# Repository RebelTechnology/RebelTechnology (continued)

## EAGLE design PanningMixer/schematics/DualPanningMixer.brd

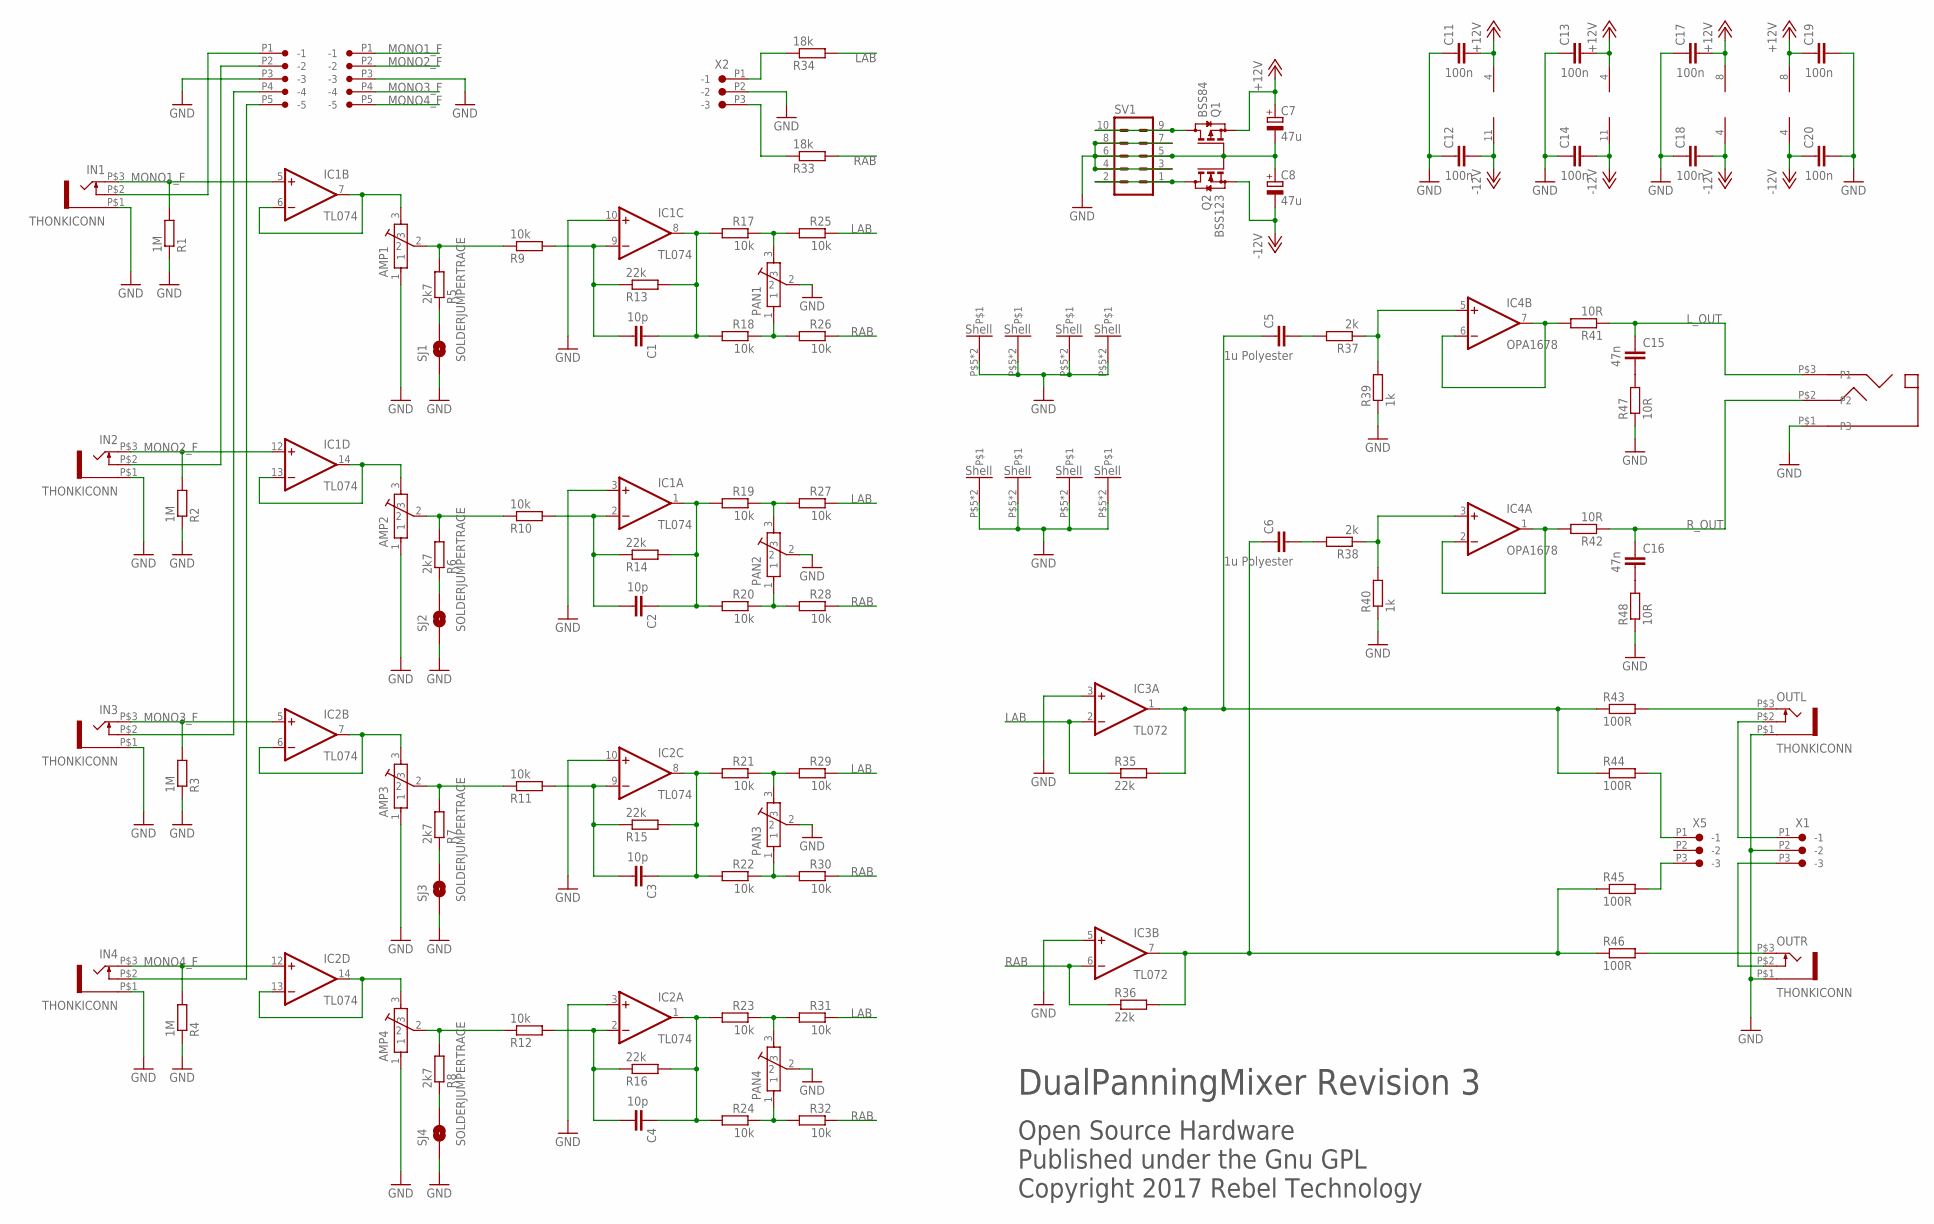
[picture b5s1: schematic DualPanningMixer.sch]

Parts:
AMP1, AMP2, AMP3, AMP4: POT-ALPS-RK09L1140
C1, C2, C3, C4: 10p; C0603
C5, C6: 1u Polyester; C1210
C7, C8: 47u; UD-5X5,8_NICHICON
C11, C12, C13, C14, C17, C18, C19, C20: 100n; C0603
C15, C16: 47n; C0603
IC1, IC2: TL074; SO14
IC3: TL072; SO08
IC4: OPA1678; SO08
IN1, IN2, IN3, IN4: THONKICONN
OUTHP: THONKICONN_STEREO
OUTL: THONKICONN
OUTR: THONKICONN
PAN1, PAN2, PAN3, PAN4: POT-ALPS-RK09L1140
Q1: BSS84; SOT23
Q2: BSS123; SOT23
R1, R2, R3, R4: 1M; 0603
R5, R6, R7, R8: 2k7; 0603
R9, R10, R11, R12, R17, R18, R19, R20, R21, R22, R23, R24, R25, R26, R27, R28, R29, R30, R31, R32: 10k; 0603
R13, R14, R15, R16, R35, R36: 22k; 0603
R33, R34: 18k; 0603
R37, R38: 2k; 0603
R39, R40: 1k; 0603
R41, R42, R47, R48: 10R; 0603
R43, R44, R45, R46: 100R; 0603
SJ1, SJ2, SJ3, SJ4: SOLDERJUMPERTRACE; SJ_2S-TRACE
SV1: MA05-2
X1, X2, X5: CON-JST_PH_3W
X3, X4: CON-JST_PH_5W

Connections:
+12V: C7.+, C11.2, C13.2, C17.2, C19.1, IC1.4 (V+), IC2.4 (V+), IC3.8 (V+), IC4.8 (V+), Q1.2 (S)
-12V: C8.-, C12.2, C14.2, C18.2, C20.1, IC1.11 (V-), IC2.11 (V-), IC3.4 (V-), IC4.4 (V-), Q2.2 (S)
GND: AMP1.1, AMP1.P$5, AMP1.P$6, AMP2.1, AMP2.P$5, AMP2.P$6, AMP3.1, AMP3.P$5, AMP3.P$6, AMP4.1, AMP4.P$5, AMP4.P$6, C7.-, C8.+, C11.1, C12.1, C13.1, C14.1, C17.1, C18.1, C19.2, C20.2, IC1.3 (+IN), IC1.10 (+IN), IC2.3 (+IN), IC2.10 (+IN), IC3.3 (+IN), IC3.5 (+IN), IN1.P$1 (5), IN2.P$1 (5), IN3.P$1 (5), IN4.P$1 (5), OUTHP.P$1 (P3), OUTL.P$1 (5), OUTR.P$1 (5), PAN1.2, PAN1.P$5, PAN1.P$6, PAN2.2, PAN2.P$5, PAN2.P$6, PAN3.2, PAN3.P$5, PAN3.P$6, PAN4.2, PAN4.P$5, PAN4.P$6, Q1.1 (G), Q2.1 (G), R1.1, R2.1, R3.1, R4.1, R39.1, R40.1, R47.1, R48.1, SJ1.1, SJ2.1, SJ3.1, SJ4.1, SV1.3, SV1.4, SV1.5, SV1.6, SV1.7, SV1.8, X1.P2 (-2), X2.P2 (-2), X3.P3 (-3), X4.P3 (-3)
LAB: IC3.2 (-IN), R25.1, R27.1, R29.1, R31.1, R34.2, R35.1
L_OUT: C15.1, OUTHP.P$3 (P1), R41.1
MONO1: AMP1.3, IC1.6 (-IN), IC1.7 (OUT)
MONO1_F: IC1.5 (+IN), IN1.P$3 (3), R1.2, X3.P1 (-1)
MONO2: AMP2.3, IC1.13 (-IN), IC1.14 (OUT)
MONO2_F: IC1.12 (+IN), IN2.P$3 (3), R2.2, X3.P2 (-2)
MONO3: AMP3.3, IC2.6 (-IN), IC2.7 (OUT)
MONO3_F: IC2.5 (+IN), IN3.P$3 (3), R3.2, X3.P4 (-4)
MONO4: AMP4.3, IC2.13 (-IN), IC2.14 (OUT)
MONO4_F: IC2.12 (+IN), IN4.P$3 (3), R4.2, X3.P5 (-5)
unnamed: AMP4.2, R8.2, R12.1
unnamed: IN2.P$2 (4), X4.P2 (-2)
unnamed: C5.1, IC3.1 (OUT), R35.2, R43.1, R44.1
unnamed: IN1.P$2 (4), X4.P1 (-1)
unnamed: C6.1, IC3.7 (OUT), R36.2, R45.1, R46.1
unnamed: IN3.P$2 (4), X4.P4 (-4)
unnamed: IC4.3 (+IN), R38.1, R40.2
unnamed: AMP1.2, R5.2, R9.1
unnamed: C1.2, IC1.9 (-IN), R9.2, R13.1
unnamed: AMP3.2, R7.2, R11.1
unnamed: AMP2.2, R6.2, R10.1
unnamed: R5.1, SJ1.2
unnamed: IC4.5 (+IN), R37.1, R39.2
unnamed: R33.1, X2.P3 (-3)
unnamed: IN4.P$2 (4), X4.P5 (-5)
unnamed: R6.1, SJ2.2
unnamed: PAN1.1, R18.1, R26.2
unnamed: PAN1.3, R17.1, R25.2
unnamed: R7.1, SJ3.2
unnamed: R8.1, SJ4.2
unnamed: C1.1, IC1.8 (OUT), R13.2, R17.2, R18.2
unnamed: R34.1, X2.P1 (-1)
unnamed: C4.1, IC2.1 (OUT), R16.2, R23.2, R24.2
unnamed: C2.1, IC1.1 (OUT), R14.2, R19.2, R20.2
unnamed: PAN2.3, R19.1, R27.2
unnamed: OUTL.P$3 (3), R43.2
unnamed: PAN2.1, R20.1, R28.2
unnamed: PAN3.3, R21.1, R29.2
unnamed: C3.1, IC2.8 (OUT), R15.2, R21.2, R22.2
unnamed: PAN3.1, R22.1, R30.2
unnamed: PAN4.3, R23.1, R31.2
unnamed: OUTR.P$3 (3), R46.2
unnamed: PAN4.1, R24.1, R32.2
unnamed: C16.2, R48.2
unnamed: C2.2, IC1.2 (-IN), R10.2, R14.1
unnamed: Q2.3 (D), SV1.1, SV1.2
unnamed: C3.2, IC2.9 (-IN), R11.2, R15.1
unnamed: Q1.3 (D), SV1.9, SV1.10
unnamed: C4.2, IC2.2 (-IN), R12.2, R16.1
unnamed: C15.2, R47.2
unnamed: C5.2, R37.2
unnamed: IC4.6 (-IN), IC4.7 (OUT), R41.2
unnamed: IC4.1 (OUT), IC4.2 (-IN), R42.2
unnamed: C6.2, R38.2
OUT_NS_L: R44.2, X5.P1 (-1)
OUT_NS_R: R45.2, X5.P3 (-3)
OUT_SW_L: OUTL.P$2 (4), X1.P1 (-1)
OUT_SW_R: OUTR.P$2 (4), X1.P3 (-3)
RAB: IC3.6 (-IN), R26.1, R28.1, R30.1, R32.1, R33.2, R36.1
R_OUT: C16.1, OUTHP.P$2 (P2), R42.1

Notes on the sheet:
Open Source Hardware Published under the Gnu GPL Copyright 2017 Rebel Technology
DualPanningMixer Revision 3

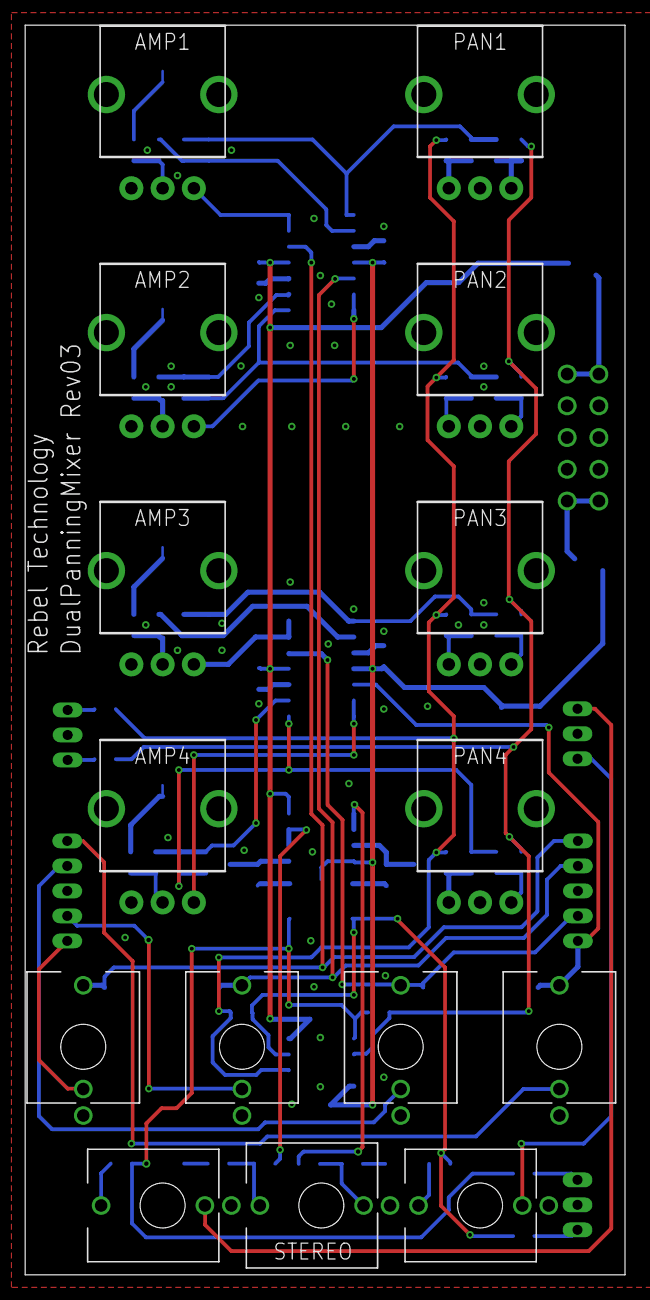
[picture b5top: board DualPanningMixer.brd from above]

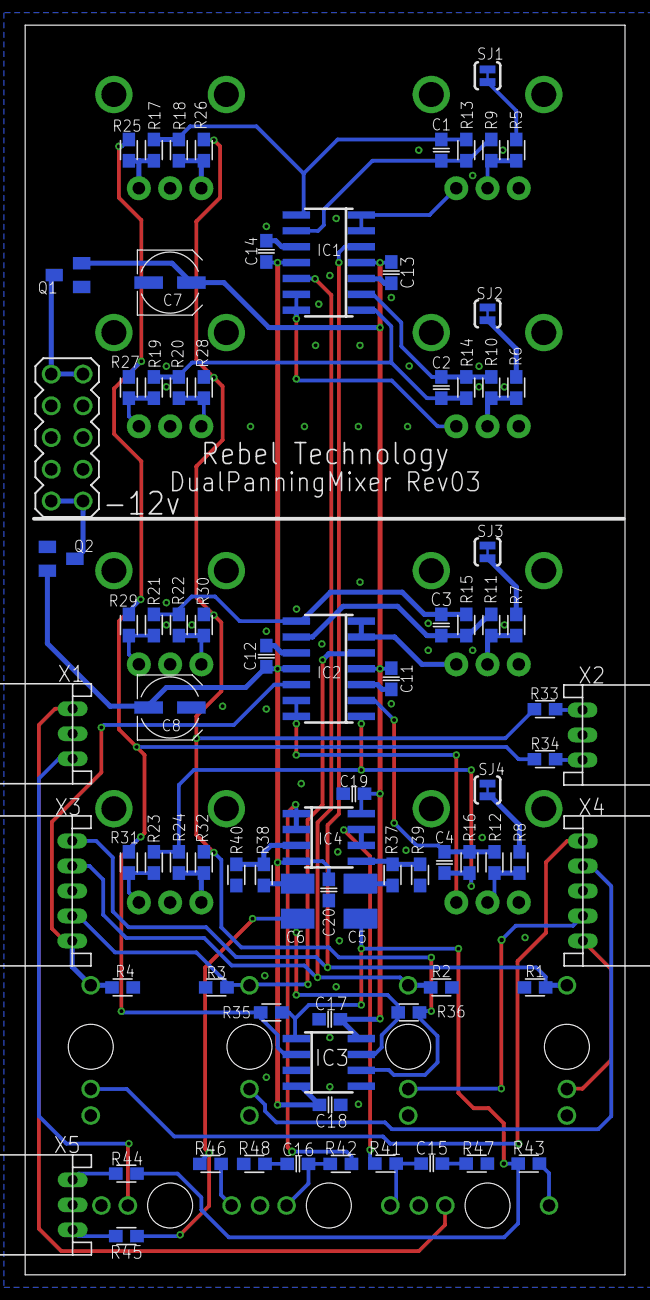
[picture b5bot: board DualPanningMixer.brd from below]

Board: 2 copper layers, 48.0 x 100.0 mm, 97 parts (82 on the bottom side), 63 nets.

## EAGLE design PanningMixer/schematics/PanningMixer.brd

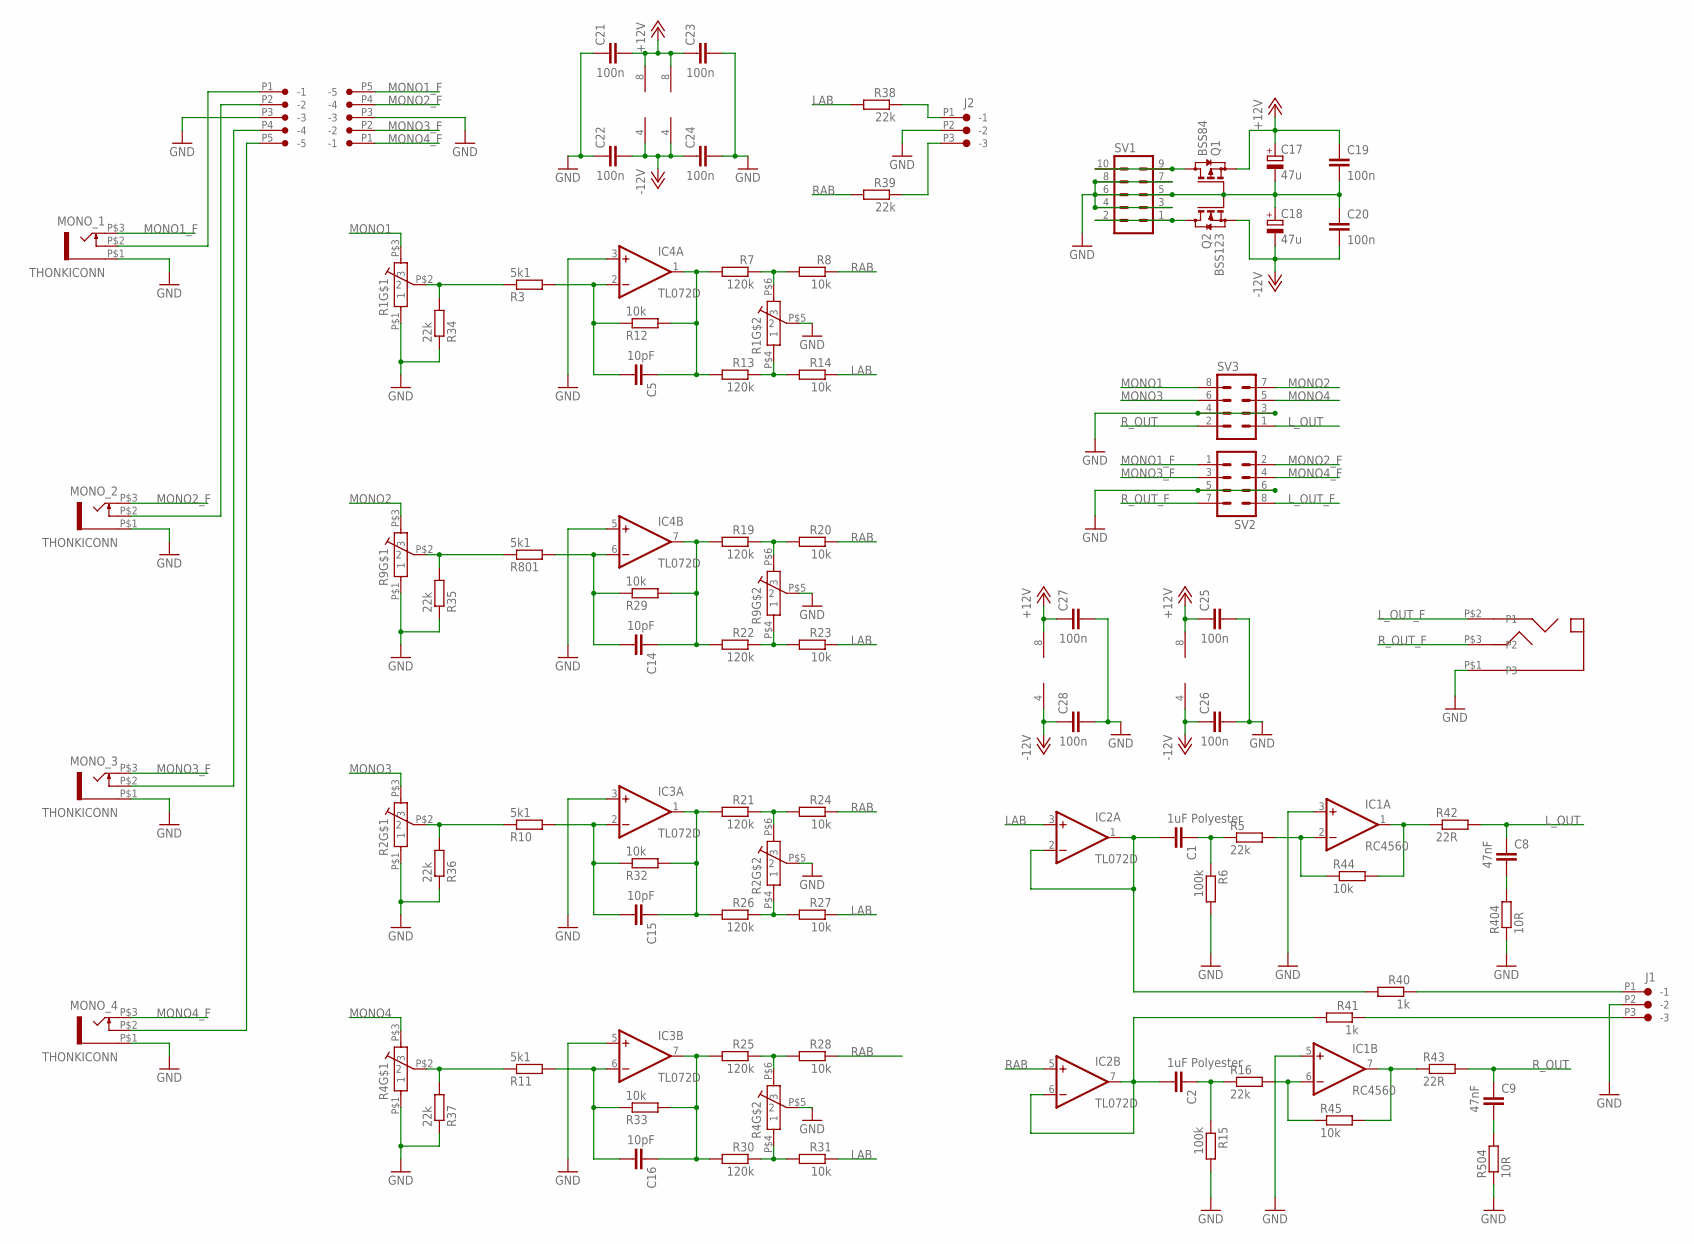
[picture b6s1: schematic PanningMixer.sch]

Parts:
C1, C2: 1uF Polyester; C1210
C5, C14, C15, C16: 10pF; C0603
C8, C9: 47nF; C0603
C17, C18: 47u; PANASONIC_B
C19, C20, C21, C22, C23, C24, C25, C26, C27, C28: 100n; C0603
IC1: RC4560; SO08
IC2, IC3, IC4: TL072D; SO08
J1, J2: CON-JST_PH_3W
MONO_1, MONO_2, MONO_3, MONO_4: THONKICONN
Q1: BSS84; SOT23
Q2: BSS123; SOT23
R1, R2, R4, R9: POT-ALPHA_DUAL_9MM; POT-ALPA_DUAL_9MM
R3, R10, R11, R801: 5k1; 0603
R5, R16, R34, R35, R36, R37, R38, R39: 22k; 0603
R6, R15: 100k; 0603
R7, R13, R19, R21, R22, R25, R26, R30: 120k; 0603
R8, R12, R14, R20, R23, R24, R27, R28, R29, R31, R32, R33, R44, R45: 10k; 0603
R40, R41: 1k; 0603
R42, R43: 22R; 0603
R404, R504: 10R; 0603
SV1: MA05-2
SV2, SV3: MA04-2
U1: CON-PROSIGNAL_MJ-355W
U2, U4: CON-JST_PH_5W

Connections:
+12V: C17.+, C19.1, C21.2, C23.1, C25.1, C27.1, IC1.8 (V+), IC2.8 (V+), IC3.8 (V+), IC4.8 (V+), Q1.2 (S)
-12V: C18.-, C20.2, C22.2, C24.1, C26.1, C28.1, IC1.4 (V-), IC2.4 (V-), IC3.4 (V-), IC4.4 (V-), Q2.2 (S)
GND: C17.-, C18.+, C19.2, C20.1, C21.1, C22.1, C23.2, C24.2, C25.2, C26.2, C27.2, C28.2, IC1.3 (+IN), IC1.5 (+IN), IC3.3 (+IN), IC3.5 (+IN), IC4.3 (+IN), IC4.5 (+IN), J1.P2 (-2), J2.P2 (-2), Q1.1 (G), Q2.1 (G), R1.P$1 (1), R1.P$5 (2), R2.P$1 (1), R2.P$5 (2), R4.P$1 (1), R4.P$5 (2), R6.2, R9.P$1 (1), R9.P$5 (2), R15.2, R34.1, R35.1, R36.1, R37.1, R404.1, R504.1, SV1.3, SV1.4, SV1.5, SV1.6, SV1.7, SV1.8, SV3.3, SV3.4
GND_A: MONO_1.P$1 (5), MONO_2.P$1 (5), MONO_3.P$1 (5), MONO_4.P$1 (5), SV2.5, SV2.6, U1.P$1 (P3), U2.P3 (-3), U4.P3 (-3)
LAB: IC2.3 (+IN), R14.1, R23.1, R27.1, R31.1, R38.2
L_OUT: C8.1, R42.2, SV3.1
L_OUT_F: SV2.8, U1.P$2 (P1)
MONO1: R1.P$3 (3), SV3.8
MONO1_F: MONO_1.P$3 (3), SV2.1, U4.P5 (-5)
MONO2: R9.P$3 (3), SV3.7
MONO2_F: MONO_2.P$3 (3), SV2.2, U4.P4 (-4)
MONO3: R2.P$3 (3), SV3.6
MONO3_F: MONO_3.P$3 (3), SV2.3, U4.P2 (-2)
MONO4: R4.P$3 (3), SV3.5
MONO4_F: MONO_4.P$3 (3), SV2.4, U4.P1 (-1)
unnamed: R4.P$2 (2), R11.1, R37.2
unnamed: MONO_2.P$2 (4), U2.P2 (-2)
unnamed: MONO_1.P$2 (4), U2.P1 (-1)
unnamed: C1.1, R5.1, R6.1
unnamed: MONO_3.P$2 (4), U2.P4 (-4)
unnamed: IC1.2 (-IN), R5.2, R44.1
unnamed: R1.P$2 (2), R3.1, R34.2
unnamed: C5.2, IC4.2 (-IN), R3.2, R12.1
unnamed: R2.P$2 (2), R10.1, R36.2
unnamed: R9.P$2 (2), R35.2, R801.1
unnamed: C9.2, R504.2
unnamed: J2.P1 (-1), R38.1
unnamed: MONO_4.P$2 (4), U2.P5 (-5)
unnamed: J1.P1 (-1), R40.1
unnamed: R1.P$4 (1), R13.1, R14.2
unnamed: R1.P$6 (3), R7.1, R8.2
unnamed: J1.P3 (-3), R41.1
unnamed: C8.2, R404.2
unnamed: C2.1, R15.1, R16.1
unnamed: C5.1, IC4.1 (OUT), R7.2, R12.2, R13.2
unnamed: J2.P3 (-3), R39.1
unnamed: C16.1, IC3.7 (OUT), R25.2, R30.2, R33.2
unnamed: C14.1, IC4.7 (OUT), R19.2, R22.2, R29.2
unnamed: IC1.1 (OUT), R42.1, R44.2
unnamed: IC1.6 (-IN), R16.2, R45.1
unnamed: C1.2, IC2.1 (OUT), IC2.2 (-IN), R40.2
unnamed: IC1.7 (OUT), R43.1, R45.2
unnamed: C2.2, IC2.6 (-IN), IC2.7 (OUT), R41.2
unnamed: R9.P$6 (3), R19.1, R20.2
unnamed: R9.P$4 (1), R22.1, R23.2
unnamed: R2.P$6 (3), R21.1, R24.2
unnamed: C15.1, IC3.1 (OUT), R21.2, R26.2, R32.2
unnamed: R2.P$4 (1), R26.1, R27.2
unnamed: R4.P$6 (3), R25.1, R28.2
unnamed: R4.P$4 (1), R30.1, R31.2
unnamed: C14.2, IC4.6 (-IN), R29.1, R801.2
unnamed: Q2.3 (D), SV1.1, SV1.2
unnamed: C15.2, IC3.2 (-IN), R10.2, R32.1
unnamed: Q1.3 (D), SV1.9, SV1.10
unnamed: C16.2, IC3.6 (-IN), R11.2, R33.1
RAB: IC2.5 (+IN), R8.1, R20.1, R24.1, R28.1, R39.2
R_OUT: C9.1, R43.2, SV3.2
R_OUT_F: SV2.7, U1.P$3 (P2)

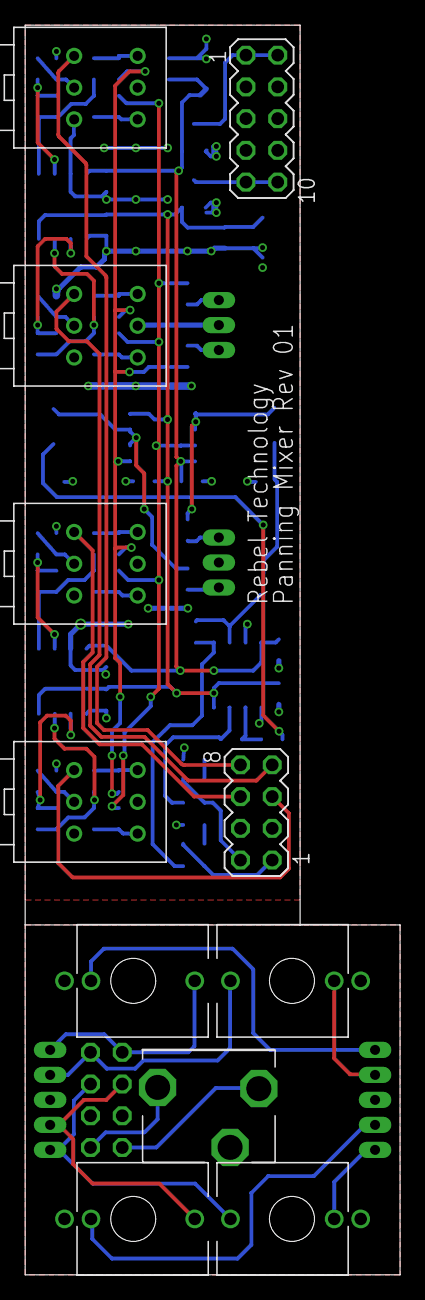
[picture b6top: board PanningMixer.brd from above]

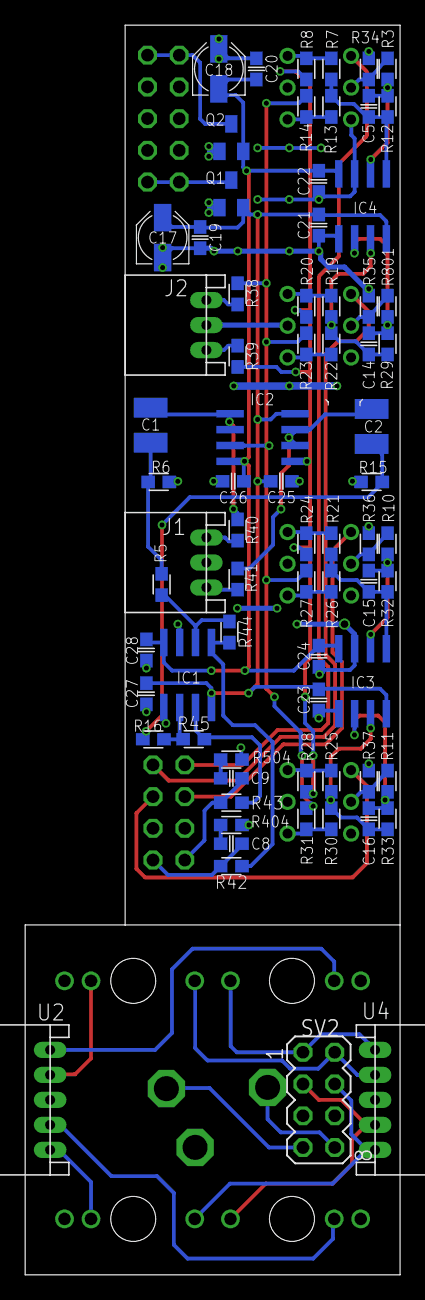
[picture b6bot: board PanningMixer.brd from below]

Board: 2 copper layers, 30.0 x 100.0 mm, 84 parts (73 on the bottom side), 58 nets.

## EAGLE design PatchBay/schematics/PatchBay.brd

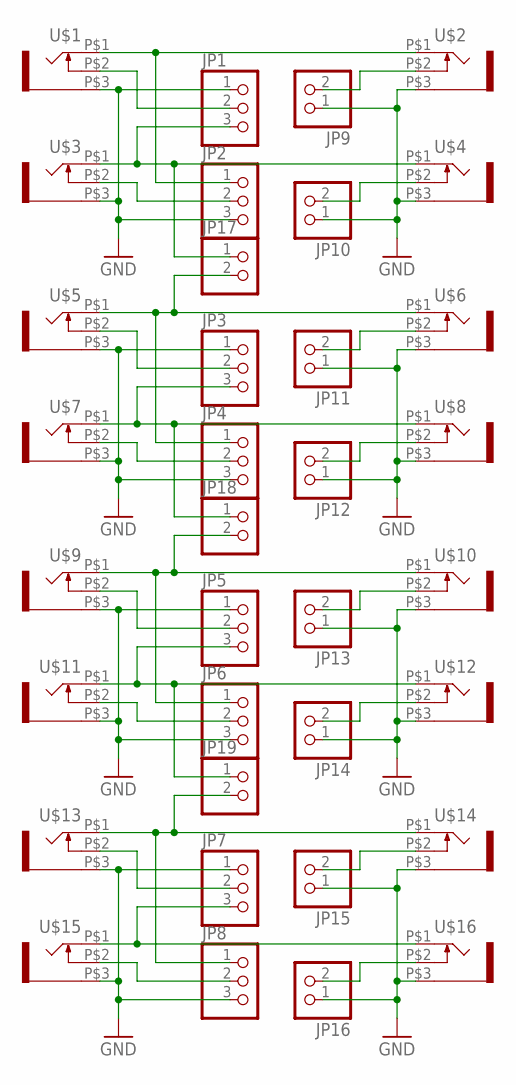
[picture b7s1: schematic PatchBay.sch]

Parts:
JP1, JP2, JP3, JP4, JP5, JP6, JP7, JP8: PINHD-1X3; 1X03
JP9, JP10, JP11, JP12, JP13, JP14, JP15, JP16, JP17, JP18, JP19: PINHD-1X2; 1X02
U$1, U$2, U$3, U$4, U$5, U$6, U$7, U$8, U$9, U$10, U$11, U$12, U$13, U$14, U$15, U$16: JACK-UJ-3502-R; UJ-3502-R

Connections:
GND: JP1.1, JP2.3, JP3.1, JP4.3, JP5.1, JP6.3, JP7.1, JP8.3, JP9.1, JP10.1, JP11.1, JP12.1, JP13.1, JP14.1, JP15.1, JP16.1, U$1.P$3 (SLEEVE), U$2.P$3 (SLEEVE), U$3.P$3 (SLEEVE), U$4.P$3 (SLEEVE), U$5.P$3 (SLEEVE), U$6.P$3 (SLEEVE), U$7.P$3 (SLEEVE), U$8.P$3 (SLEEVE), U$9.P$3 (SLEEVE), U$10.P$3 (SLEEVE), U$11.P$3 (SLEEVE), U$12.P$3 (SLEEVE), U$13.P$3 (SLEEVE), U$14.P$3 (SLEEVE), U$15.P$3 (SLEEVE), U$16.P$3 (SLEEVE)
unnamed: JP1.3, JP17.1, U$3.P$1 (TIP), U$4.P$1 (TIP)
unnamed: JP2.1, U$1.P$1 (TIP), U$2.P$1 (TIP)
unnamed: JP1.2, U$1.P$2 (SW)
unnamed: JP2.2, U$3.P$2 (SW)
unnamed: JP3.3, JP18.1, U$7.P$1 (TIP), U$8.P$1 (TIP)
unnamed: JP4.1, JP17.2, U$5.P$1 (TIP), U$6.P$1 (TIP)
unnamed: JP3.2, U$5.P$2 (SW)
unnamed: JP4.2, U$7.P$2 (SW)
unnamed: JP5.3, JP19.1, U$11.P$1 (TIP), U$12.P$1 (TIP)
unnamed: JP6.1, JP18.2, U$9.P$1 (TIP), U$10.P$1 (TIP)
unnamed: JP5.2, U$9.P$2 (SW)
unnamed: JP6.2, U$11.P$2 (SW)
unnamed: JP7.3, U$15.P$1 (TIP), U$16.P$1 (TIP)
unnamed: JP8.1, JP19.2, U$13.P$1 (TIP), U$14.P$1 (TIP)
unnamed: JP7.2, U$13.P$2 (SW)
unnamed: JP8.2, U$15.P$2 (SW)
unnamed: JP14.2, U$12.P$2 (SW)
unnamed: JP13.2, U$10.P$2 (SW)
unnamed: JP12.2, U$8.P$2 (SW)
unnamed: JP11.2, U$6.P$2 (SW)
unnamed: JP10.2, U$4.P$2 (SW)
unnamed: JP9.2, U$2.P$2 (SW)
unnamed: JP15.2, U$14.P$2 (SW)
unnamed: JP16.2, U$16.P$2 (SW)

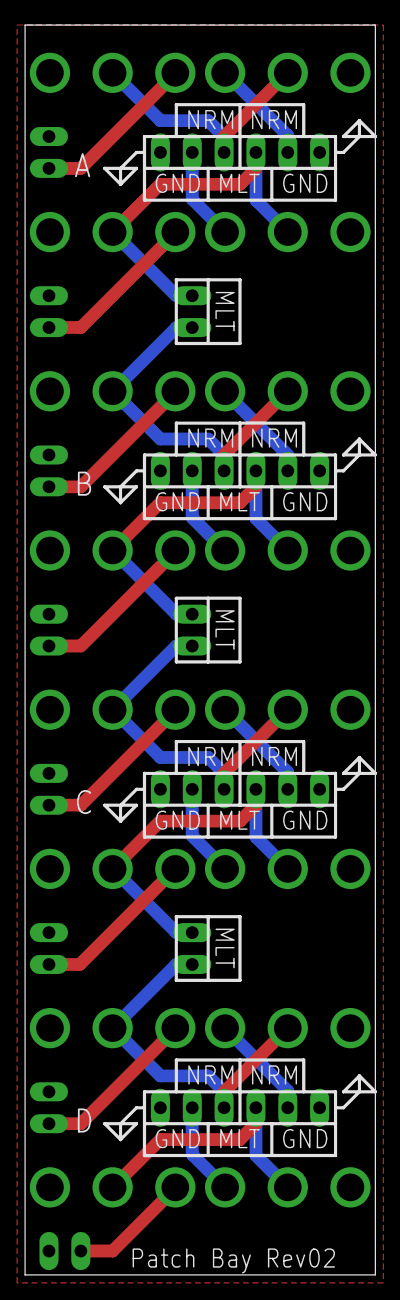
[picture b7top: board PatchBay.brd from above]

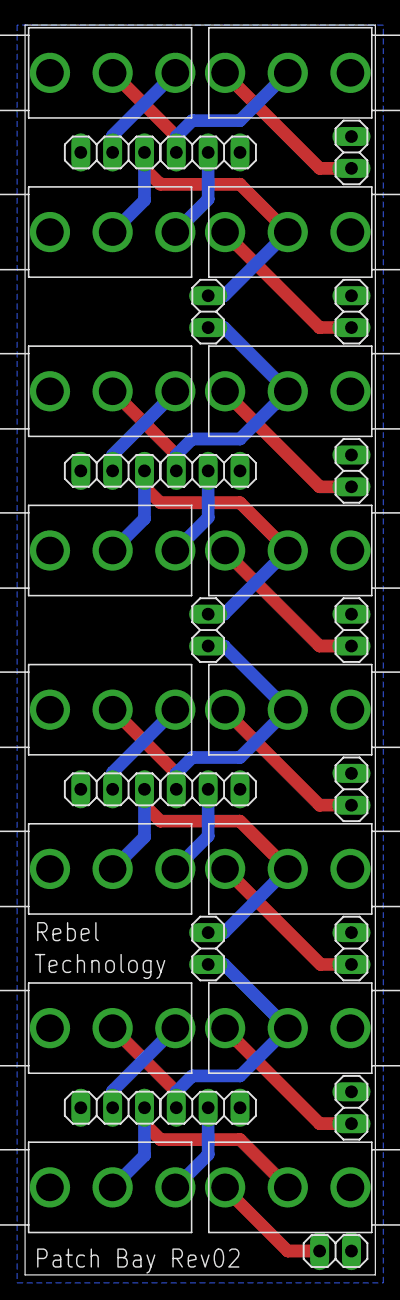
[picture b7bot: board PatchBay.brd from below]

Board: 2 copper layers, 27.9 x 99.7 mm, 35 parts (35 on the bottom side), 25 nets.
